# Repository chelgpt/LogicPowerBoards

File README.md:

# LogicPowerBoards

KiCad/KiCanvas workspace for the Docreate 002 modernization boards.

This repository is prepared for browser-based review through GitHub Pages + KiCanvas.

## Boards

- PowerBoard: 24V input, 5V / 20A isolated DC-DC board based on Mornsun URF2405QB-100WR3.
- LogicBoard: 24V input, 12V / 6W isolated DC-DC board based on Mornsun URB2412ZP-6WR3.

## Viewer

After enabling GitHub Pages from `main` / `docs`, open:

- `https://chelgpt.github.io/LogicPowerBoards/power.html`
- `https://chelgpt.github.io/LogicPowerBoards/logic.html`

Status: initial AI-assisted clean starter, not yet production-approved. Final manufacturing requires datasheet pinout verification, ERC/DRC, Gerber review, and ideally human EE review.

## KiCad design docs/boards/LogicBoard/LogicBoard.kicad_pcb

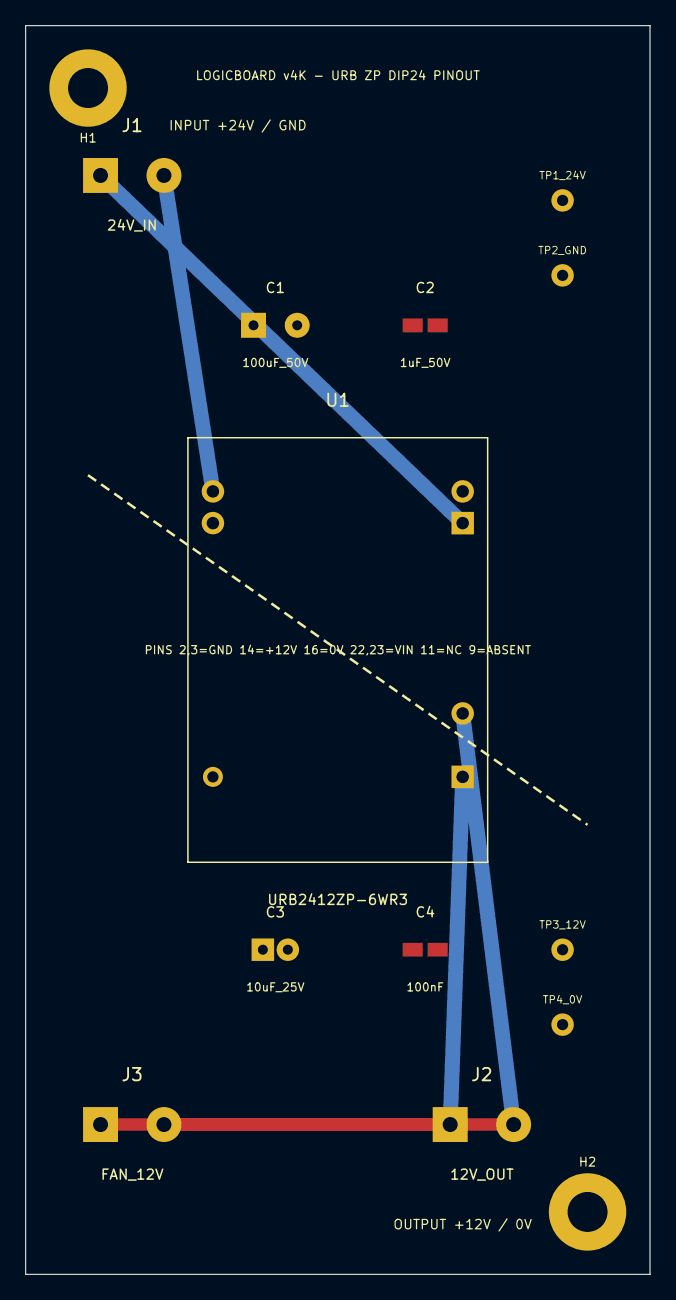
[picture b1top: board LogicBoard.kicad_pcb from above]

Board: 2 copper layers, 50.0 x 100.0 mm, 14 parts (0 on the bottom side), 4 nets.

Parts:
C1: 100uF_50V; CP_Radial
C2: 1uF_50V; C1206
C3: 10uF_25V; CP_Radial
C4: 100nF; C1206
H1, H2: MountingHole_M3
J1: 24V_IN; Terminal_2P_5_08
J2: 12V_OUT; Terminal_2P_5_08
J3: FAN_12V; Terminal_2P_5_08
TP1_24V, TP2_GND, TP3_12V, TP4_0V: TP1mm
U1: URB2412ZP-6WR3; Mornsun_URB2412ZP_6WR3_DIP24

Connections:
GND_IN: C1.2, C2.2, J1.2, TP2_GND.1, U1.2, U1.3
GND_OUT: C3.2, C4.2, J2.2, J3.2, TP4_0V.1, U1.16
OUT_12V: C3.1, C4.1, J2.1, J3.1, TP3_12V.1, U1.14
VIN_24V: C1.1, C2.1, J1.1, TP1_24V.1, U1.22, U1.23

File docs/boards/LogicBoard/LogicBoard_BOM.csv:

Reference,Qty,Value,Package,Notes
U1,1,URB2412ZP-6WR3,DIP24 grid TH,Populated pins 2 3 GND 11 NC 14 +Vo 16 0V 22 23 Vin
J1,1,24V input terminal 2P,5.08mm,Input from 24V rail
J2,1,12V output terminal 2P,5.08mm,Output to logic rail
J3,1,12V fan output terminal 2P,5.08mm,Optional fan output
C1,1,100uF 50V low ESR,THT radial,Input bulk capacitor
C2,1,1uF 50V,1206 ceramic,Input HF capacitor close to U1
C3,1,10uF 25V low ESR,THT radial,Output bulk capacitor
C4,1,100nF 25V,1206 ceramic,Output HF capacitor close to U1
TP1 TP2 TP3 TP4,4,Test points,1mm pad,+24V GND +12V 0V

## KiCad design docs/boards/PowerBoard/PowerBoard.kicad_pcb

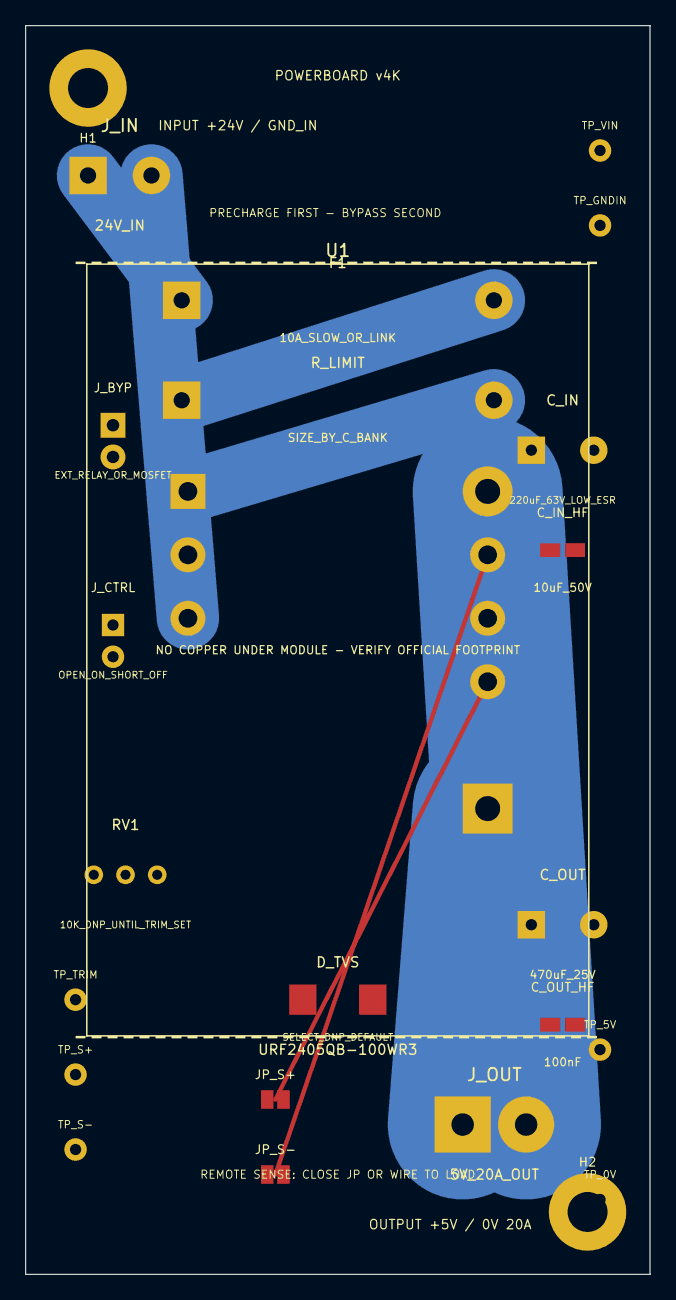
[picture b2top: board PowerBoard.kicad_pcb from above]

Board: 2 copper layers, 50.0 x 100.0 mm, 24 parts (0 on the bottom side), 10 nets.

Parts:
C_IN: 220uF_63V_LOW_ESR; CP_Radial
C_IN_HF: 10uF_50V; C1206
C_OUT: 470uF_25V; CP_Radial
C_OUT_HF: 100nF; C1206
D_TVS: SELECT_DNP_DEFAULT; TVS_SMC_SELECT
F1: 10A_SLOW_OR_LINK; Fuse_or_Link_10A
H1, H2: MountingHole_M3
JP_S+: Sense_Jumper_Plus
JP_S-: Sense_Jumper_Minus
J_BYP: EXT_RELAY_OR_MOSFET; External_Bypass_Header
J_CTRL: OPEN_ON_SHORT_OFF; Header_1x2
J_IN: 24V_IN; Terminal_IN_2P
J_OUT: 5V_20A_OUT; Terminal_OUT_2P_30A
RV1: 10K_DNP_UNTIL_TRIM_SET; Trim_3296W
R_LIMIT: SIZE_BY_C_BANK; Precharge_R
TP_0V, TP_5V: TP1mm
TP_GNDIN: TP1mm
TP_S+: TP1mm
TP_S-: TP1mm
TP_TRIM: TP1mm
TP_VIN: TP1mm
U1: URF2405QB-100WR3; Mornsun_URF2405QB_100WR3_QB

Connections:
CTRL: J_CTRL.1, U1.2
GND_IN: C_IN.2, C_IN_HF.2, J_CTRL.2, J_IN.2, TP_GNDIN.1, U1.3
OUT_0V: C_OUT.2, C_OUT_HF.2, D_TVS.2, JP_S-.2, J_OUT.2, TP_0V.1, U1.4
OUT_5V: C_OUT.1, C_OUT_HF.1, D_TVS.1, JP_S+.2, J_OUT.1, TP_5V.1, U1.8
SENSE_N: JP_S-.1, RV1.1, TP_S-.1, U1.5
SENSE_P: JP_S+.1, RV1.3, TP_S+.1, U1.7
TRIM: RV1.2, TP_TRIM.1, U1.6
VIN_24V: F1.1, J_IN.1, TP_VIN.1
VIN_AFTER_F1: F1.2, J_BYP.1, R_LIMIT.1
VIN_TO_MODULE: C_IN.1, C_IN_HF.1, J_BYP.2, R_LIMIT.2, U1.1

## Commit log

2026-06-13 Initialize LogicPowerBoards README
2026-06-13 Add production checklist
2026-06-13 Add KiCanvas index page
2026-06-13 Add viewer stylesheet
2026-06-13 Add PowerBoard viewer placeholder
2026-06-13 Add LogicBoard viewer placeholder
2026-06-13 Disable Jekyll for GitHub Pages
2026-06-13 Add PowerBoard project file
2026-06-13 Add LogicBoard project file
2026-06-13 Add LogicBoard PCB starter
2026-06-13 Add simplified PowerBoard PCB starter
2026-06-13 Add PowerBoard schematic placeholder
2026-06-13 Add LogicBoard schematic placeholder
2026-06-13 Add tabbed board viewer index
2026-06-13 Add critique and remake plan
2026-06-13 Remake LogicBoard PCB to v4A functional layout
2026-06-13 Remake PowerBoard PCB to v4A functional architecture
2026-06-13 Add PowerBoard BOM
2026-06-13 Add LogicBoard BOM
2026-06-13 Add manufacturing notes and release gates
2026-06-13 Add current project status
2026-06-13 Update index status to v4B and add engineering links
2026-06-14 tmp test
2026-06-14 tmp update test
2026-06-14 v4C fix LogicBoard to URB ZP DIP24 footprint
2026-06-14 v4C fix PowerBoard URF drills and add required blocks
2026-06-14 Remove temporary connector test file
2026-06-14 Update status after v4C audit-driven fixes
2026-06-14 v4C update LogicBoard BOM
2026-06-14 Add AI audit synthesis v4C
2026-06-14 Add v4D release gates
2026-06-14 Add PowerBoard precharge requirements v4D
2026-06-14 Add KiCad DRC rules v4D
2026-06-14 Update index to v4D engineering review state
2026-06-14 Update status to v4D review gate iteration
2026-06-14 v4E set PowerBoard KiCad net classes
2026-06-14 v4E set LogicBoard KiCad net classes
2026-06-14 Add v4E locked netlist reference
2026-06-14 Add fab readiness scorecard v4E
2026-06-14 Update status to v4E netlist and DRC lock iteration
2026-06-14 Update index to v4E netlist lock state
2026-06-14 v4F generate real LogicBoard schematic from netlist lock
2026-06-14 v4F generate real PowerBoard schematic from netlist lock
2026-06-14 Update status to v4F schematic generation iteration
2026-06-14 Add fab readiness scorecard v4F
2026-06-14 Update index to v4F schematic state
2026-06-14 Add repository validation script
2026-06-14 Add KiCad export script
2026-06-14 Add KiCad CI workflow
2026-06-14 Update status to v4G CI validation pipeline
2026-06-14 Add fab readiness scorecard v4G
2026-06-14 Update index to v4G CI pipeline state
2026-06-14 v4H pause push CI to stop failing email loop
2026-06-14 v4H fix validator to v4G status and scorecard
2026-06-14 Update status to v4H CI failure triage
2026-06-14 v4I add lightweight push text validation workflow
2026-06-14 v4I make validator version-tolerant
2026-06-14 Update status to v4I split workflow stabilization
2026-06-14 Add v4J fabrication package manifest
2026-06-14 Update status to v4J fab package manifest
2026-06-14 v4K add PowerBoard testpoints mounting holes and silkscreen guards
2026-06-14 v4K add LogicBoard testpoints mounting holes and polarity labels
2026-06-14 v4K extend validator for testpoints and mounting holes
2026-06-14 Add fab readiness scorecard v4K
2026-06-14 Update status to v4K mechanical completeness pass
2026-06-14 Update index to v4K mechanical completeness state
2026-06-14 Add v4L engineering freeze decision
2026-06-14 Update status to v4L engineering freeze
2026-06-14 v4M fix validator for v4L freeze status
2026-06-14 v4M align PowerBoard BOM with v4K PCB state
2026-06-14 v4M align LogicBoard BOM with v4K PCB state
2026-06-14 Add v4M BOM audit against original specification
2026-06-14 Add v4M assembly and bring-up procedure
2026-06-14 Add v4M production gate decision matrix
2026-06-14 Update status to v4M BOM and production gate pass
2026-06-14 Update index to v4M BOM and production gate state
